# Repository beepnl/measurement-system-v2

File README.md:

# BEEP - Measurement system
This is a repo containing the files to create the open source hardware for the Beep measurement system.

## Measurement system parts

The measurement system casing is designed as both an electonics/sensor housing, as well as a weighing frame. The outer casing is assembled in four pieces (2 tops, 2 bottoms) out of 18mm thick plate 'Betonplex' (glued multiplex with water resistant top and bottom layer). The wooden top and bottom are connected together by the 2 weight sensor (aluminium) blocks, held in place by 2 weight sensor brackets each. The left and right part are held together with 2 stainless steel tubes, that are screwed on the wood. At one side tightly, using wood parkers, at the other side loosely, using m4 bolts that go inside the inserts. By this connection, the total size of the frame is adjustable for different types of hives. 

## Frame
The folder 'frame' contains two folders: wood and stainless steel. 

### Wood
The 2D drawings in both Illustrator format and DXF (required by most milling parties).

This is a picture of the milling software, with which we mill 42 pieces (21 tops, 21 bottoms) out of an 2440 x 1220 x 18 mm Betonplex.

### Stainless steel
The 3D and 2D drawings of the stainless steel tube, and the sensor bracket are in this folder. They can be ordered at companies lasering steel.

## Electronics
The electronics of the measurement system are bundled together on the Beep PCB, which connects an Arduino, a LoRa (wireless network) chip and the sensors via Grove connectors together.

The folder 'electronics' contains two folders: gerber and kicad.

With the Gerber files, you can directly order a PCB. It contains all files required for the manufacturing of the PCB. 

With the Kicad files, you can edit the PCB and it's components in the open source PCB creation software Kicad (http://kicad.org/).

### Schematic

*NB: There is an error in the PCB, the one wire temperature sensor DS18b20 cannot work on analog port A7 (the A6 and A7 IO pins can only be used as analog pins, not as digital IO). So you have to use A4, or A5 to connect one wire sensor(s) to. So you also have to add the 4k7 resistor between V+ and the one wire data pin yourself, since the resistor on the PCB is connected to V+ and A7.*

The schematic can be found in the PDF (https://github.com/beepnl/measurement-system-v2/blob/master/electronics/Beep-pcb-v1.4-schematic.pdf)

### PCB

### Assembly

## Firmware
In the 'firmware' folder, the ultra low power Arduino code is shared to use with the PCB and complete the measurement system.

Place the folder 'Beep-low-power' inside your Arduino folder and set up your own LoRa connection details to send the data.
Send an e-mail to pim@beep.nl, to add your Measurement system Device EUI to your Beep app account and receive it's measurements in the app.

## Improvements
If you have improvements, or ideas for creating a better frame, please send an e-mail to pim@beep.nl explaining your thoughts. Or just fork this repo, and do a pull request with you adjustments, or additions.

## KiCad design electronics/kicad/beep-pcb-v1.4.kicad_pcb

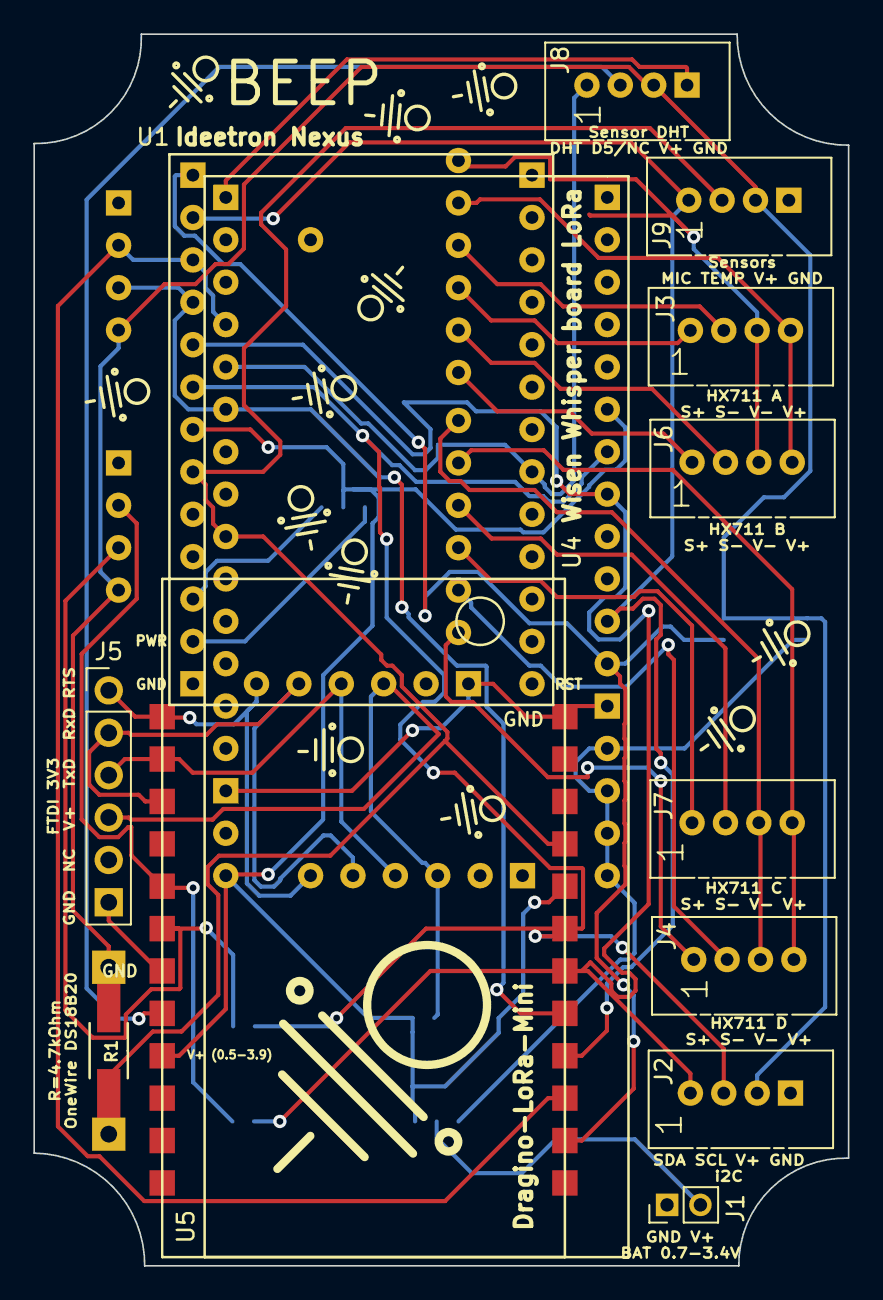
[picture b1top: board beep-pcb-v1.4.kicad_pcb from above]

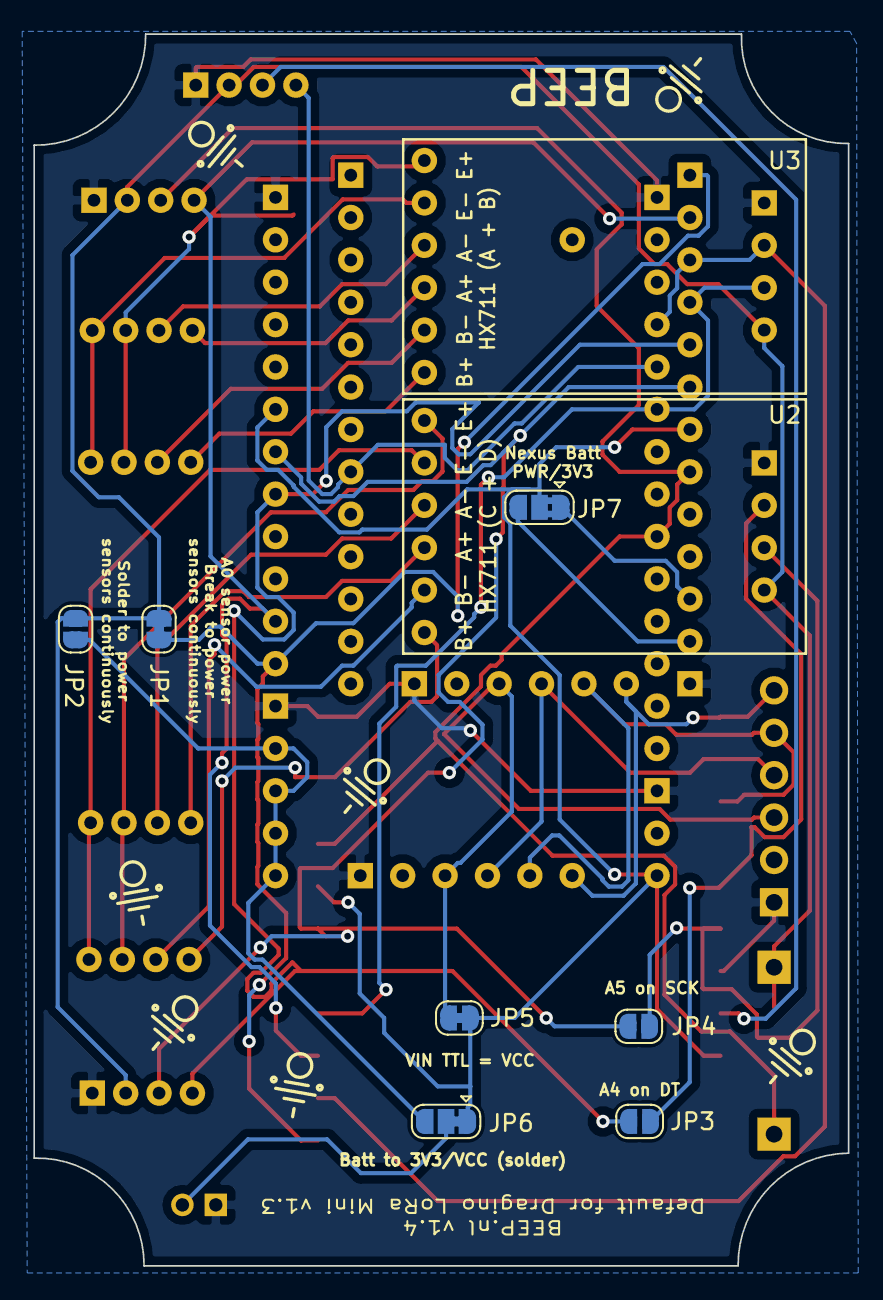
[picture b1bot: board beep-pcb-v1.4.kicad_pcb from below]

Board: 2 copper layers, 48.8 x 73.8 mm, 22 parts (9 on the bottom side), 34 nets.

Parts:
J1: Power; Pin_Header_Straight_1x02_Pitch2.00mm
J2: Grove I2C, 1=SDA, 2=SCL; Grove_1x04
J3: Weight A/ALL; Grove_1x04
J4: Weight D; Grove_1x04
J5: 3V3 TTL FTDI; Pin_Header_Straight_1x06_Pitch2.54mm
J6: Weight B; Grove_1x04
J7: Weight C; Grove_1x04
J8: Grove 1=DHT22, 2=NC/D5 Dragino; Grove_1x04
J9: Grove 1=Mic, 2=DS18B20; Grove_1x04
JP1: Sensor switchable power; SolderJumper-2_P1.3mm_Bridged_RoundedPad1.0x1.5mm
JP2: Sensor continuous power; SolderJumper-2_P1.3mm_Open_RoundedPad1.0x1.5mm
JP3: A4 on DT; SolderJumper-2_P1.3mm_Open_RoundedPad1.0x1.5mm
JP4: A5 on SCK; SolderJumper-2_P1.3mm_Open_RoundedPad1.0x1.5mm
JP5: VIN TTL = VCC; SolderJumper-2_P1.3mm_Bridged_RoundedPad1.0x1.5mm
JP6: Batt to VCC/3V3 (solder); SolderJumper-3_P1.3mm_Bridged12_RoundedPad1.0x1.5mm
JP7: Nexus Batt -> 3V3/PWR; SolderJumper-3_P1.3mm_Bridged2Bar12_RoundedPad1.0x1.5mm
R1: R; Resistor_SMD+THTuniversal_1206_RM10_HandSoldering
U1: Nexus
U2, U3: HX711
U4: Whisper LoRa; Whisper_Lora
U5: Dragino-LoRa-Mini; Dragino LoRa Mini

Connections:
+3V3: JP2.1, JP6.3, U4.29, U4.30, U4.31, U4.32
+BATT: J1.2, JP6.2
+VDC: JP5.2, JP6.1, JP7.2, U1.7, U4.17, U4.40, U5.9, U5.20
GND: J1.1, J2.4, J5.6, J8.4, J9.4, U1.1, U1.27, U2.10, U3.10, U4.1, U4.15, U4.27, U4.33, U4.45, U5.7, U5.24
unnamed: J2.1, JP3.2, U1.9, U4.38, U5.18
unnamed: J2.2, JP4.2, U1.8, U4.39, U5.19
unnamed: J2.3, J8.3, J9.3, JP1.2, JP2.2, R1.1, U2.7, U3.7
unnamed: J3.1, U3.4
unnamed: J3.2, U3.3
unnamed: J3.3, J6.3, U3.1
unnamed: J3.4, J6.4, U3.2
unnamed: J4.1, U2.6
unnamed: J4.2, U2.5
unnamed: J4.3, J7.3, U2.1
unnamed: J4.4, J7.4, U2.2
unnamed: J5.1, U1.32, U4.22, U5.1
unnamed: J5.2, U1.31, U4.23, U5.3
unnamed: J5.3, U1.30, U4.24, U5.2
unnamed: J5.4, JP5.1, U1.29, U4.25
unnamed: J6.1, U3.6
unnamed: J6.2, U3.5
unnamed: J7.1, U2.4
unnamed: J7.2, U2.3
unnamed: J8.1, U1.19, U4.5
unnamed: J8.2, U5.8
unnamed: J9.1, U1.12, U4.35, U5.15
unnamed: J9.2, R1.2, U1.6, U4.9, U5.21
unnamed: JP1.1, U1.13, U4.34, U5.14
unnamed: JP3.1, U2.9, U5.5
unnamed: JP4.1, U2.8, U5.6
unnamed: JP7.1, U1.3
unnamed: JP7.3, U1.2
unnamed: U1.10, U3.8, U4.6, U5.17
unnamed: U1.11, U3.9, U4.4, U5.16

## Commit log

2018-10-01 Included all drawings
2018-10-01 Added PCB files
2018-10-01 Cleaned up folders
2018-10-03 Added firmware
2018-10-03 Readme update
2018-11-12 Bug in PCB: Changed One wire DS18b20 sensor from A7 to A4
    There is an error in the PCB, the one wire temperature sensor DS18b20 cannot work on analog port A7 (the A6 and A7 IO pins can only be used as analog pins, not as digital IO). So you have to use A4, 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
2019-02-13 Update to v9
    - Changed amount of measurements
    - Changed DHT library
    - Added measurement value 'compression' for small payload
2019-02-22 Added TTN HTTP integration converters
2021-02-03 Update README.md
    Changed /raw into /blob for link fixing
2021-11-09 Update README.md
    https://forum.kicad.info/t/warning-avoid-all-links-to-kicad-pcb-org-use-kicad-org/31521
